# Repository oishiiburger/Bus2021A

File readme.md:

# Bus 2021A

This is a quick n' dirty bus design for a hobbyist computer system based around the [WD65C02](https://en.wikipedia.org/wiki/WDC_65C02). It is not meant to be fancy, but it should be functional. Features of the 65C02 which are unique to the WDC version are not exposed to the bus (i.e. VPB Vector-Pull Output, MLB Memory-Lock Output, and BE Bus Enable input). 4 pins (USER1 through USER4) are provided for peripheral expansion / experimentation / whatever.

The purpose of the bus is to allow for the use of a custom backplane so that several small boards to be easily connected. The backplane design is below, and protoboards intended for this bus are to come.

The bus mapping is [here](./Bus2021A.txt), but also printed on the backplane board.

## Bus 2021A backplane - 5 slot

The backplane features spots for 5 female pin headers, a DJ jack for 5v power and a power jumper (which can be broken out to a switch), a power LED, and a reset switch which is tied into the bus. 

A future revision might include blinkenlights on the backplane, but for now there will be space for those to be easily placed on one of the protoboards.

| PCB | Schematic |
| --- | --- |
|  |  |

Necessary kicad files are in [Bus2021A_5Slot](./Bus2021A_5Slot).

## Bus 2021A Protoboard

The protoboard is intended to connect with the backplane using a 90-degree pin header. It is designed as an easy and straightforward platform to interface with the bus and features a total project grid of 30x40 (1200 solder points). It has power rails vertically on either side with ground also horizontal on row 6, and the bus overall extends into the first three rows from the bottom (effectively a stripboard), all to keep distances shorter for wiring. The project grid not counting the rails or bus extension is 912 solder points. The board is labeled front and back on both axes.

The overall layout is:

```
Rows 1-3    :   Bus extension
Rows 4-5    :   Connected vertically
Rows 7-30   :   Project space (between power rails)
```

The purpose of the vertical connection between rows 4 and 5 is for easy installation of blinkenlights on the board using individual LEDs and resistors or LED bar graphs and resistor arrays. These rows can also be used for arbitrary circut connections without having to solder and resolder multiple wires.

Necessary files are [here](./Bus2021A_Protoboard).

| Protoboard front | Protoboard rear |
| --- | --- |
|  |  |

## Symbols / footprints

A symbol for the bus and a footprint for the headers on the protoboard are in the [library folder](./Bus2021A_library).

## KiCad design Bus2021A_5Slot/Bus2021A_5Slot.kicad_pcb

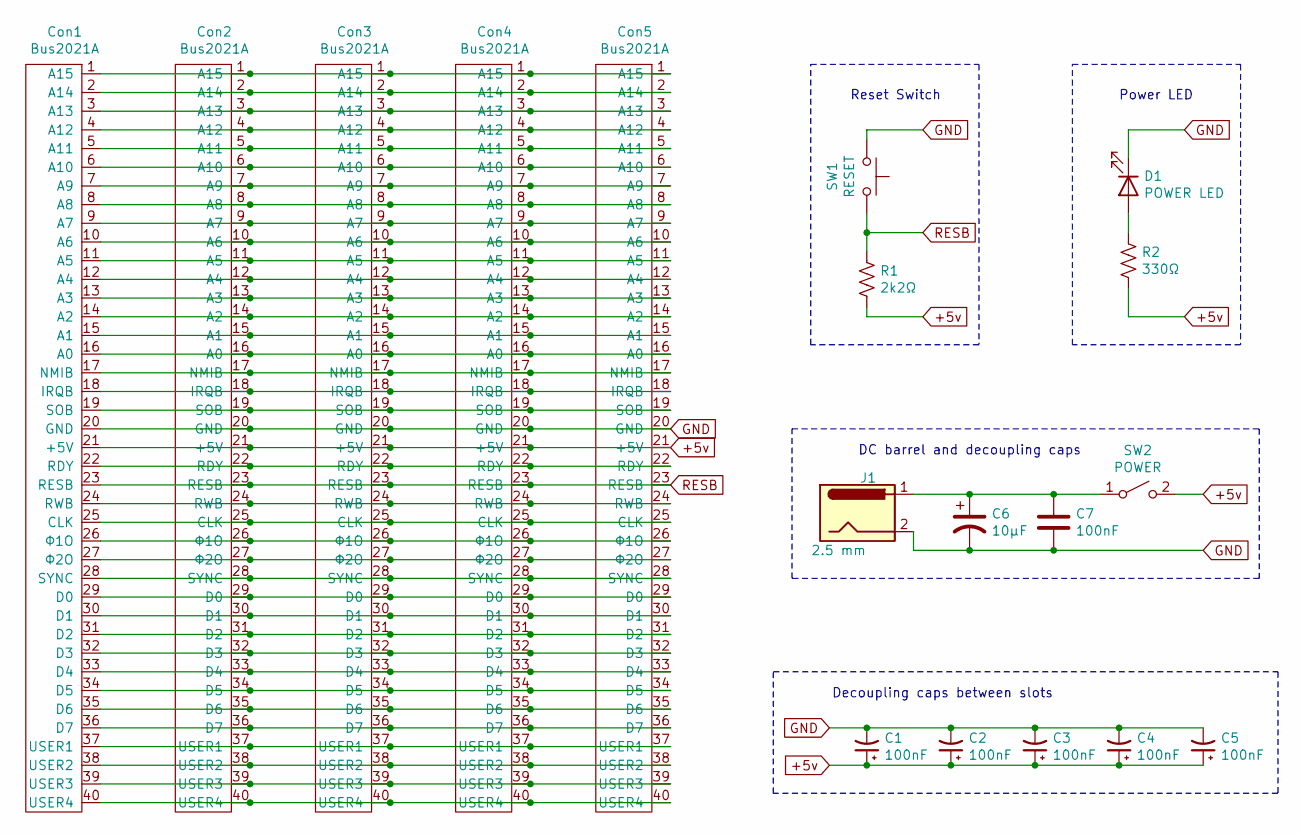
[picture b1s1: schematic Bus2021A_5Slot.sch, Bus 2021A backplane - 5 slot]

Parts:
C1, C2, C3, C4, C5, C7: 100nF; C_Disc_D3.0mm_W1.6mm_P2.50mm
C6: 10μF; CP_Radial_D5.0mm_P2.00mm
Con1, Con2, Con3, Con4, Con5: Bus2021A; PinSocket_1x40_P2.54mm_Vertical
D1: POWER LED; LED_D5.0mm
J1: 2.5 mm; BarrelJack_Horizontal
R1: 2k2Ω; R_Axial_DIN0204_L3.6mm_D1.6mm_P7.62mm_Horizontal
R2: 330Ω; R_Axial_DIN0204_L3.6mm_D1.6mm_P7.62mm_Horizontal
SW1: RESET; SW_Tactile_Straight_KSL0Axx1LFTR
SW2: POWER; PinHeader_1x02_P2.54mm_Vertical

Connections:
+5v: C1.1, C2.1, C3.1, C4.1, C5.1, Con1.21 (+5V), Con2.21 (+5V), Con3.21 (+5V), Con4.21 (+5V), Con5.21 (+5V), R1.2, R2.2, SW2.2 (B)
GND: C1.2, C2.2, C3.2, C4.2, C5.2, C6.2, C7.2, Con1.20 (GND), Con2.20 (GND), Con3.20 (GND), Con4.20 (GND), Con5.20 (GND), D1.1 (K), J1.2, SW1.1
unnamed: C6.1, C7.1, J1.1, SW2.1 (A)
unnamed: Con1.1 (A15), Con2.1 (A15), Con3.1 (A15), Con4.1 (A15), Con5.1 (A15)
unnamed: Con1.2 (A14), Con2.2 (A14), Con3.2 (A14), Con4.2 (A14), Con5.2 (A14)
unnamed: Con1.3 (A13), Con2.3 (A13), Con3.3 (A13), Con4.3 (A13), Con5.3 (A13)
unnamed: Con1.4 (A12), Con2.4 (A12), Con3.4 (A12), Con4.4 (A12), Con5.4 (A12)
unnamed: Con1.5 (A11), Con2.5 (A11), Con3.5 (A11), Con4.5 (A11), Con5.5 (A11)
unnamed: Con1.6 (A10), Con2.6 (A10), Con3.6 (A10), Con4.6 (A10), Con5.6 (A10)
unnamed: Con1.7 (A9), Con2.7 (A9), Con3.7 (A9), Con4.7 (A9), Con5.7 (A9)
unnamed: Con1.8 (A8), Con2.8 (A8), Con3.8 (A8), Con4.8 (A8), Con5.8 (A8)
unnamed: Con1.9 (A7), Con2.9 (A7), Con3.9 (A7), Con4.9 (A7), Con5.9 (A7)
unnamed: Con1.10 (A6), Con2.10 (A6), Con3.10 (A6), Con4.10 (A6), Con5.10 (A6)
unnamed: Con1.11 (A5), Con2.11 (A5), Con3.11 (A5), Con4.11 (A5), Con5.11 (A5)
unnamed: Con1.12 (A4), Con2.12 (A4), Con3.12 (A4), Con4.12 (A4), Con5.12 (A4)
unnamed: Con1.13 (A3), Con2.13 (A3), Con3.13 (A3), Con4.13 (A3), Con5.13 (A3)
unnamed: Con1.14 (A2), Con2.14 (A2), Con3.14 (A2), Con4.14 (A2), Con5.14 (A2)
unnamed: Con1.15 (A1), Con2.15 (A1), Con3.15 (A1), Con4.15 (A1), Con5.15 (A1)
unnamed: Con1.16 (A0), Con2.16 (A0), Con3.16 (A0), Con4.16 (A0), Con5.16 (A0)
unnamed: Con1.17 (NMIB), Con2.17 (NMIB), Con3.17 (NMIB), Con4.17 (NMIB), Con5.17 (NMIB)
unnamed: Con1.18 (IRQB), Con2.18 (IRQB), Con3.18 (IRQB), Con4.18 (IRQB), Con5.18 (IRQB)
unnamed: Con1.19 (SOB), Con2.19 (SOB), Con3.19 (SOB), Con4.19 (SOB), Con5.19 (SOB)
unnamed: Con1.22 (RDY), Con2.22 (RDY), Con3.22 (RDY), Con4.22 (RDY), Con5.22 (RDY)
unnamed: Con1.24 (RWB), Con2.24 (RWB), Con3.24 (RWB), Con4.24 (RWB), Con5.24 (RWB)
unnamed: Con1.25 (CLK), Con2.25 (CLK), Con3.25 (CLK), Con4.25 (CLK), Con5.25 (CLK)
unnamed: Con1.26 (Φ1O), Con2.26 (Φ1O), Con3.26 (Φ1O), Con4.26 (Φ1O), Con5.26 (Φ1O)
unnamed: Con1.27 (Φ2O), Con2.27 (Φ2O), Con3.27 (Φ2O), Con4.27 (Φ2O), Con5.27 (Φ2O)
unnamed: Con1.28 (SYNC), Con2.28 (SYNC), Con3.28 (SYNC), Con4.28 (SYNC), Con5.28 (SYNC)
unnamed: Con1.29 (D0), Con2.29 (D0), Con3.29 (D0), Con4.29 (D0), Con5.29 (D0)
unnamed: Con1.30 (D1), Con2.30 (D1), Con3.30 (D1), Con4.30 (D1), Con5.30 (D1)
unnamed: Con1.31 (D2), Con2.31 (D2), Con3.31 (D2), Con4.31 (D2), Con5.31 (D2)
unnamed: Con1.32 (D3), Con2.32 (D3), Con3.32 (D3), Con4.32 (D3), Con5.32 (D3)
unnamed: Con1.33 (D4), Con2.33 (D4), Con3.33 (D4), Con4.33 (D4), Con5.33 (D4)
unnamed: Con1.34 (D5), Con2.34 (D5), Con3.34 (D5), Con4.34 (D5), Con5.34 (D5)
unnamed: Con1.35 (D6), Con2.35 (D6), Con3.35 (D6), Con4.35 (D6), Con5.35 (D6)
unnamed: Con1.36 (D7), Con2.36 (D7), Con3.36 (D7), Con4.36 (D7), Con5.36 (D7)
unnamed: Con1.37 (USER1), Con2.37 (USER1), Con3.37 (USER1), Con4.37 (USER1), Con5.37 (USER1)
unnamed: Con1.38 (USER2), Con2.38 (USER2), Con3.38 (USER2), Con4.38 (USER2), Con5.38 (USER2)
unnamed: Con1.39 (USER3), Con2.39 (USER3), Con3.39 (USER3), Con4.39 (USER3), Con5.39 (USER3)
unnamed: Con1.40 (USER4), Con2.40 (USER4), Con3.40 (USER4), Con4.40 (USER4), Con5.40 (USER4)
unnamed: D1.2 (A), R2.1
RESB: Con1.23 (RESB), Con2.23 (RESB), Con3.23 (RESB), Con4.23 (RESB), Con5.23 (RESB), R1.1, SW1.2

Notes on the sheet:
Reset Switch
Power LED
DC barrel and decoupling caps
Decoupling caps between slots

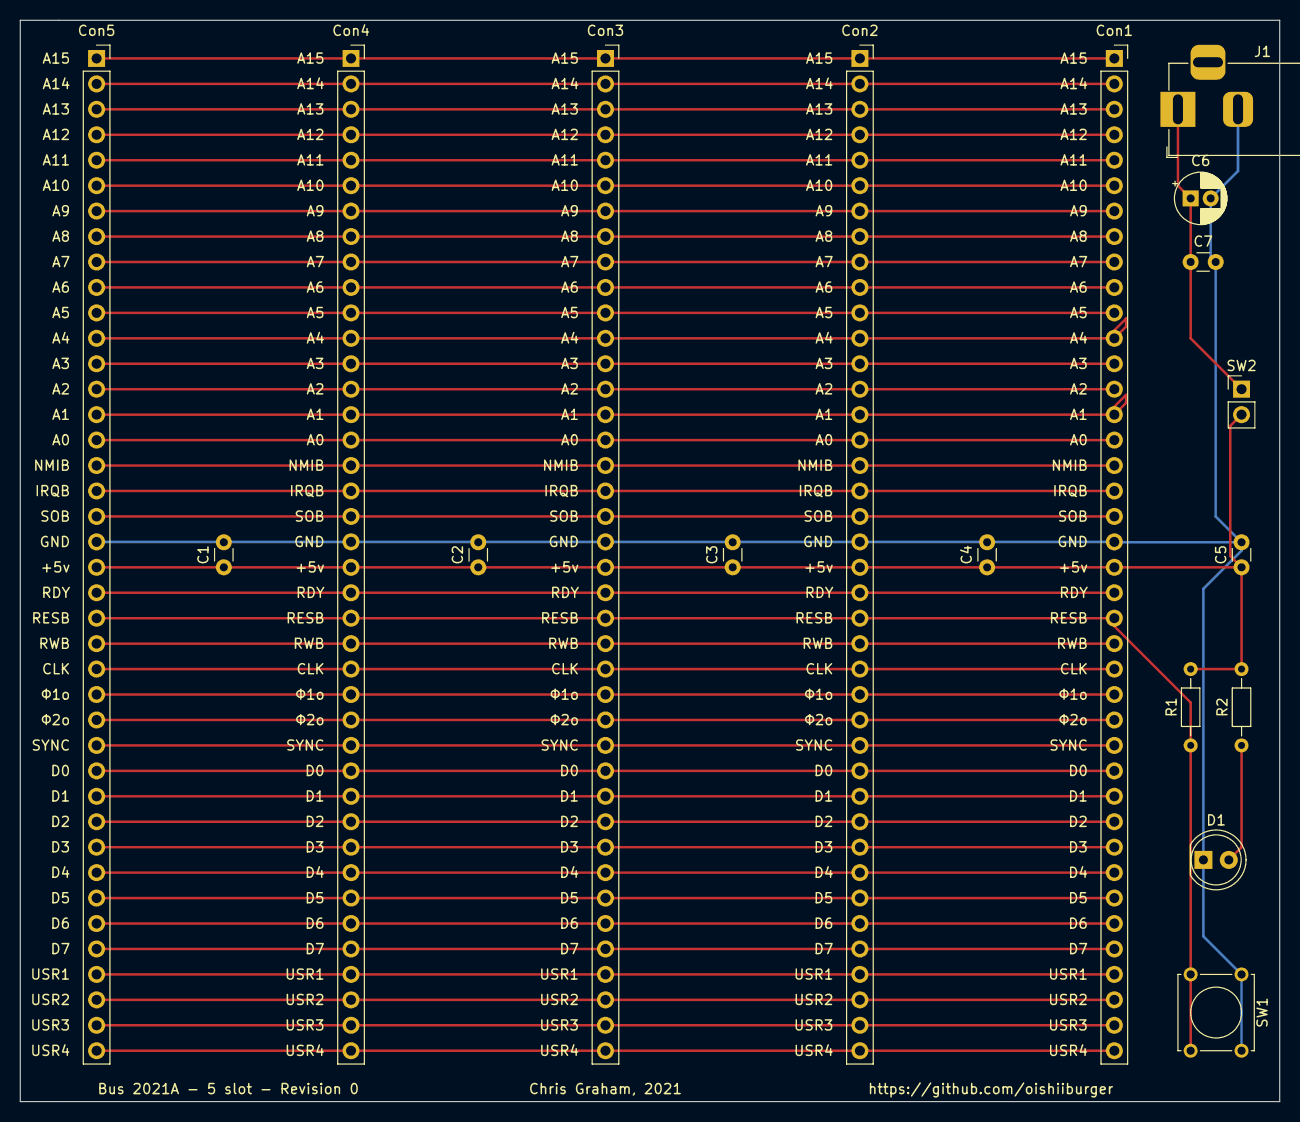
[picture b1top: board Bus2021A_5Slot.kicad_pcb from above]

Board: 2 copper layers, 125.7 x 108.0 mm, 18 parts (0 on the bottom side), 42 nets.

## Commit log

2021-08-13 Initial commit.
2021-08-13 Updated bus layout.
2021-08-13 Added Rev0 5 slot schematic and gerbers
2021-08-13 Added PCB image
2021-08-14 Added protoboard gerbers; updated readme
2021-08-14 Reorganized
2021-08-14 Typo fix
2021-08-14 Image updates
2021-08-15 Cleaned up files
2021-08-15 Edited readme
